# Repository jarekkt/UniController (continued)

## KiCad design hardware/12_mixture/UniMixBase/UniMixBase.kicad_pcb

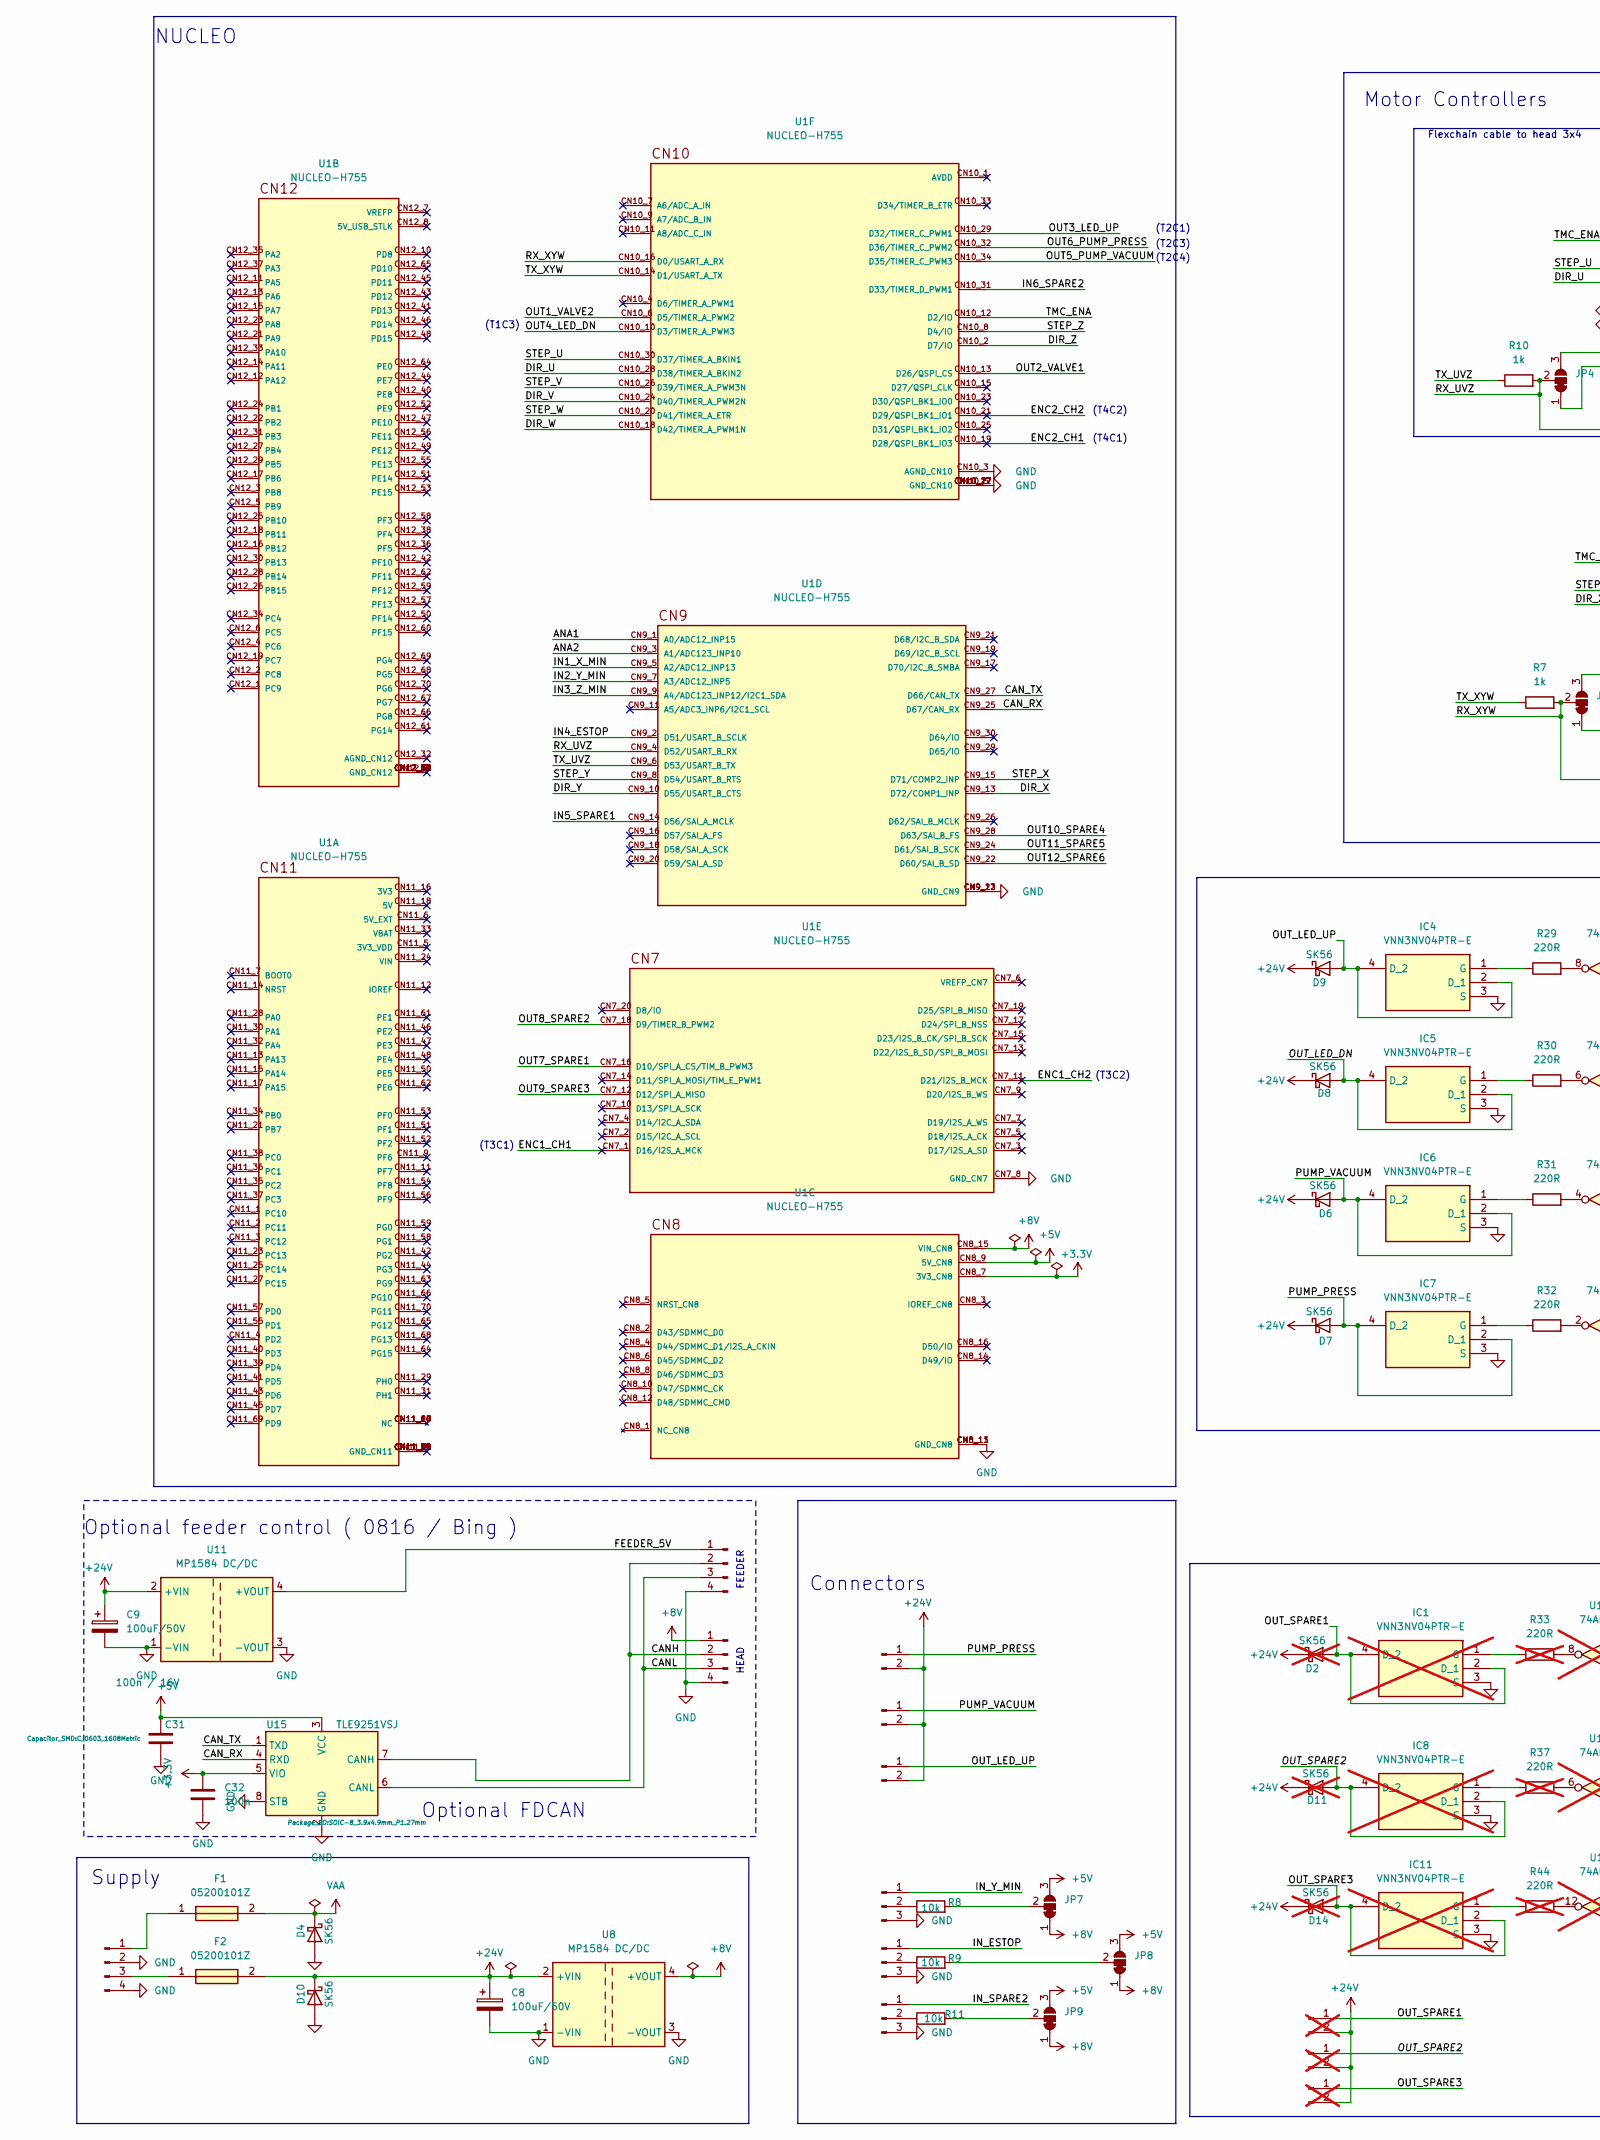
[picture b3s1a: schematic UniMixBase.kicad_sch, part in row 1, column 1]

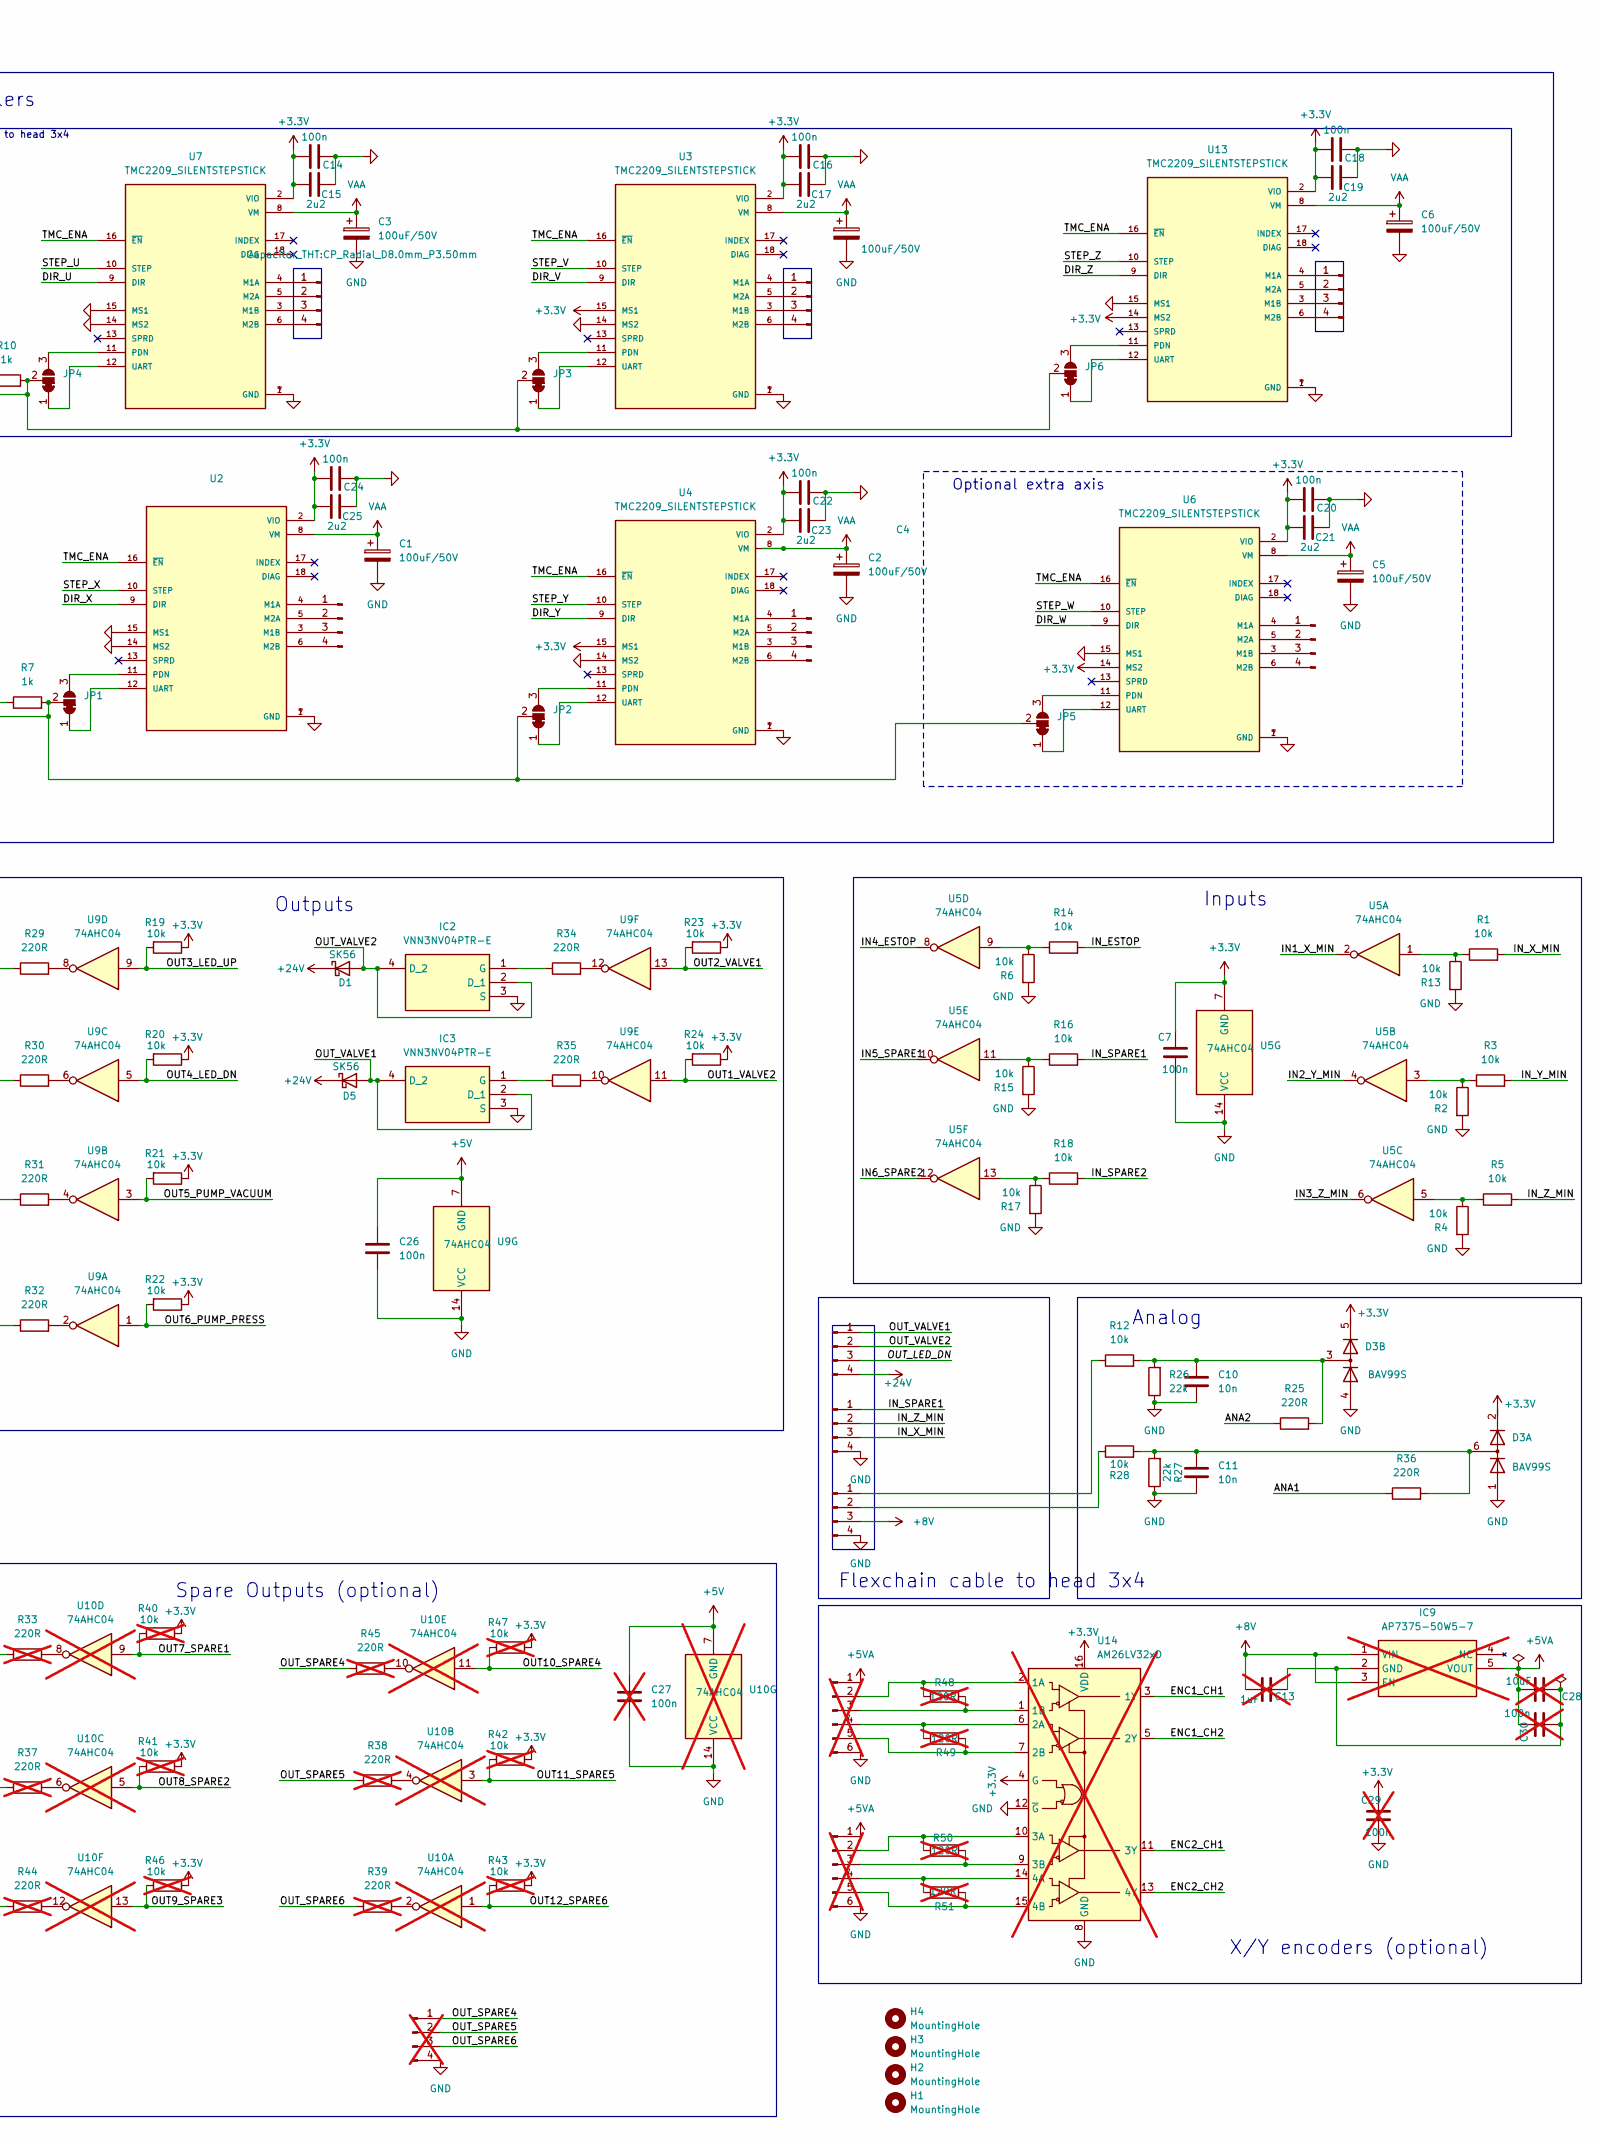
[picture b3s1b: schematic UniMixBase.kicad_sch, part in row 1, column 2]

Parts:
C1, C2, C3, C4, C5, C6, C8, C9: 100uF/50V; CP_Radial_D8.0mm_P3.50mm
C7, C14, C16, C18, C20, C22, C24, C26, C32: 100n; C_0603_1608Metric
C10, C11: 10n; C_0603_1608Metric
C13: 1uF; C_0603_1608Metric; not fitted
C15, C17, C19, C21, C23, C25: 2u2; C_0603_1608Metric
C27, C29, C30: 100n; C_0603_1608Metric; not fitted
C28: 10uF; C_1206_3216Metric; not fitted
C31: 100n / 16V; C_0603_1608Metric; Digikey CC0402KRX7R7BB104
D1, D4, D5, D6, D7, D8, D9, D10: SK56; D_SMB
D2, D11, D14: SK56; D_SMB; not fitted
D3: BAV99S; SOT-363_SC-70-6
F1, F2: 05200101Z
H1, H2, H3, H4: MountingHole; MountingHole_3.2mm_M3
IC1, IC8, IC11: VNN3NV04PTR-E; SOT230P700X180-4N; Manufacturer_Part_Number VNN3NV04PTR-E; Mouser Part Number 511-VNN3NV04PTR-E; not fitted
IC2, IC3, IC4, IC5, IC6, IC7: VNN3NV04PTR-E; SOT230P700X180-4N; Manufacturer_Part_Number VNN3NV04PTR-E; Mouser Part Number 511-VNN3NV04PTR-E
IC9: AP7375-50W5-7; SOT95P285X140-5N; Manufacturer_Part_Number AP7375-50W5-7; Mouser Part Number 621-AP7375-50W5-7; not fitted
J1, J2, J3, J4, J5, J7, J8, J9, J18, J20, J21: Conn_01x04_Male; JST_XH_B4B-XH-AM_1x04_P2.50mm_Vertical
J6, J10, J22: Conn_01x03_Pin; JST_XH_B3B-XH-A_1x03_P2.50mm_Vertical
J11, J12, J13: Conn_01x02_Male; JST_XH_B2B-XH-A_1x02_P2.50mm_Vertical; not fitted
J14: Conn_01x04_Male; JST_XH_B4B-XH-AM_1x04_P2.50mm_Vertical; not fitted
J15, J16: Conn_01x06_Male; JST_XH_B6B-XH-AM_1x06_P2.50mm_Vertical; not fitted
J24: Conn_01x04_Male; TerminalBlock_Phoenix_MKDS-1,5-4-5.08_1x04_P5.08mm_Horizont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
J31, J32, J33: Conn_01x02_Male; JST_XH_B2B-XH-A_1x02_P2.50mm_Vertical
JP1, JP2, JP3, JP4, JP5, JP6, JP7, JP8, JP9: SolderJumper_3_Bridged12; SolderJumper-3_P1.3mm_Bridged12_RoundedPad1.0x1.5mm
R1, R2, R3, R4, R5, R6, R8, R9, R11, R12, R13, R14, R15, R16, R17, R18, R19, R20, R21, R22, R23, R24, R28: 10k; R_0603_1608Metric
R7, R10: 1k; R_0603_1608Metric
R25, R29, R30, R31, R32, R34, R35, R36: 220R; R_0603_1608Metric
R26, R27: 22k; R_0603_1608Metric
R33, R37, R38, R39, R44, R45: 220R; R_0603_1608Metric; not fitted
R40, R41, R42, R43, R46, R47: 10k; R_0603_1608Metric; not fitted
R48, R49, R50, R51: 120R; R_1206_3216Metric; not fitted
U1: NUCLEO-H755; MODULE_NUCLEO-H753ZI; PARTREV Rev. 2
U2, U3, U4, U6, U7, U13: TMC2209_SILENTSTEPSTICK; MODULE_TMC2209_SILENTSTEPSTICK; PARTREV 1.20
U5, U9: 74AHC04; SOIC-14_3.9x8.7mm_P1.27mm
U8, U11: MP1584 DC/DC; MP1584_mod
U10: 74AHC04; SOIC-14_3.9x8.7mm_P1.27mm; not fitted
U14: AM26LV32xD; SOIC-16_3.9x9.9mm_P1.27mm; not fitted
U15: TLE9251VSJ; SOIC-8_3.9x4.9mm_P1.27mm; Digikey TLE9251VSJXUMA1TR-ND

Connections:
+3.3V: C7.1, C14.2, C15.2, C16.2, C17.2, C18.2, C19.2, C20.2, C21.2, C22.2, C23.2, C24.2, C25.2, C29.1, C32.1, D3.2 (K2), D3.5 (K4), R19.1, R20.1, R21.1, R22.1, R23.1, R24.1, R40.1, R41.1, R42.1, R43.1, R46.1, R47.1, U1.CN8_7 (3V3_CN8), U2.2 (VIO), U3.2 (VIO), U3.15 (MS1), U4.2 (VIO), U4.15 (MS1), U5.7 (GND), U6.2 (VIO), U6.14 (MS2), U7.2 (VIO), U13.2 (VIO), U13.14 (MS2), U14.4 (G), U14.16 (VDD), U15.5 (VIO)
+5V: C26.1, C27.1, C31.1, JP7.3 (B), JP8.3 (B), JP9.3 (B), U1.CN8_9 (5V_CN8), U9.7 (GND), U10.7 (GND), U15.3 (VCC)
+5VA: C28.1, C30.1, IC9.5 (VOUT), J15.1, J16.1
+8V: C13.1, IC9.1 (VIN), IC9.3 (EN), J8.1, J20.3, JP7.1 (A), JP8.1 (A), JP9.1 (A), U1.CN8_15 (VIN_CN8), U8.4 (+VOUT)
+24V: C8.1, C9.1, D1.1 (K), D2.1 (K), D5.1 (K), D6.1 (K), D7.1 (K), D8.1 (K), D9.1 (K), D10.1 (K), D11.1 (K), D14.1 (K), F2.2, J11.2, J12.2, J13.2, J18.4, J31.2, J32.2, J33.2, U8.2 (+VIN), U11.2 (+VIN)
/ANA1: R36.1, U1.CN9_1 (A0/ADC12_INP15)
/ANA2: R25.1, U1.CN9_3 (A1/ADC123_INP10)
/CANH: J5.2, J8.2, U15.7 (CANH)
/CANL: J5.3, J8.3, U15.6 (CANL)
/CAN_RX: U1.CN9_25 (D67/CAN_RX), U15.4 (RXD)
/CAN_TX: U1.CN9_27 (D66/CAN_TX), U15.1 (TXD)
/DIR_U: U1.CN10_28 (D38/TIMER_A_BKIN2), U7.9 (DIR)
/DIR_V: U1.CN10_24 (D40/TIMER_A_PWM2N), U3.9 (DIR)
/DIR_W: U1.CN10_18 (D42/TIMER_A_PWM1N), U6.9 (DIR)
/DIR_X: U1.CN9_13 (D72/COMP1_INP), U2.9 (DIR)
/DIR_Y: U1.CN9_10 (D55/USART_B_CTS), U4.9 (DIR)
/DIR_Z: U1.CN10_2 (D7/IO), U13.9 (DIR)
/ENC1_CH1: U1.CN7_1 (D16/I2S_A_MCK), U14.3 (1Y)
/ENC1_CH2: U1.CN7_11 (D21/I2S_B_MCK), U14.5 (2Y)
/ENC2_CH1: U1.CN10_19 (D28/QSPI_BK1_IO3), U14.11 (3Y)
/ENC2_CH2: U1.CN10_21 (D29/QSPI_BK1_IO1), U14.13 (4Y)
/FEEDER_5V: J5.1, U11.4 (+VOUT)
/IN1_X_MIN: U1.CN9_5 (A2/ADC12_INP13), U5.2
/IN2_Y_MIN: U1.CN9_7 (A3/ADC12_INP5), U5.4
/IN3_Z_MIN: U1.CN9_9 (A4/ADC123_INP12/I2C1_SDA), U5.6
/IN4_ESTOP: U1.CN9_2 (D51/USART_B_SCLK), U5.8
/IN5_SPARE1: U1.CN9_14 (D56/SAI_A_MCLK), U5.10
/IN6_SPARE2: U1.CN10_31 (D33/TIMER_D_PWM1), U5.12
/IN_ESTOP: J22.1, R14.2
/IN_SPARE1: J21.1, R16.2
/IN_SPARE2: J10.1, R18.2
/IN_X_MIN: J21.3, R1.2
/IN_Y_MIN: J6.1, R3.2
/IN_Z_MIN: J21.2, R5.2
/OUT1_VALVE2: R24.2, U1.CN10_6 (D5/TIMER_A_PWM2), U9.11
/OUT2_VALVE1: R23.2, U1.CN10_13 (D26/QSPI_CS), U9.13
/OUT3_LED_UP: R19.2, U1.CN10_29 (D32/TIMER_C_PWM1), U9.9
/OUT4_LED_DN: R20.2, U1.CN10_10 (D3/TIMER_A_PWM3), U9.5
/OUT5_PUMP_VACUUM: R21.2, U1.CN10_34 (D35/TIMER_C_PWM3), U9.3
/OUT6_PUMP_PRESS: R22.2, U1.CN10_32 (D36/TIMER_C_PWM2), U9.1
/OUT7_SPARE1: R40.2, U1.CN7_16 (D10/SPI_A_CS/TIM_B_PWM3), U10.9
/OUT8_SPARE2: R41.2, U1.CN7_18 (D9/TIMER_B_PWM2), U10.5
/OUT9_SPARE3: R46.2, U1.CN7_12 (D12/SPI_A_MISO), U10.13
/OUT10_SPARE4: R47.2, U1.CN9_28 (D63/SAI_B_FS), U10.11
/OUT11_SPARE5: R42.2, U1.CN9_24 (D61/SAI_B_SCK), U10.3
/OUT12_SPARE6: R43.2, U1.CN9_22 (D60/SAI_B_SD), U10.1
/OUT_LED_DN: D8.2 (A), IC5.2 (D_1), IC5.4 (D_2), J18.3
/OUT_LED_UP: D9.2 (A), IC4.2 (D_1), IC4.4 (D_2), J33.1
/OUT_SPARE1: D2.2 (A), IC1.2 (D_1), IC1.4 (D_2), J11.1
/OUT_SPARE2: D11.2 (A), IC8.2 (D_1), IC8.4 (D_2), J12.1
/OUT_SPARE3: D14.2 (A), IC11.2 (D_1), IC11.4 (D_2), J13.1
/OUT_SPARE4: J14.1, R45.1
/OUT_SPARE5: J14.2, R38.1
/OUT_SPARE6: J14.3, R39.1
/OUT_VALVE1: D5.2 (A), IC3.2 (D_1), IC3.4 (D_2), J18.1
/OUT_VALVE2: D1.2 (A), IC2.2 (D_1), IC2.4 (D_2), J18.2
/PUMP_PRESS: D7.2 (A), IC7.2 (D_1), IC7.4 (D_2), J32.1
/PUMP_VACUUM: D6.2 (A), IC6.2 (D_1), IC6.4 (D_2), J31.1
/RX_UVZ: JP3.2 (C), JP4.2 (C), JP6.2 (C), R10.2, U1.CN9_4 (D52/USART_B_RX)
/RX_XYW: JP1.2 (C), JP2.2 (C), JP5.2 (C), R7.2, U1.CN10_16 (D0/USART_A_RX)
/STEP_U: U1.CN10_30 (D37/TIMER_A_BKIN1), U7.10 (STEP)
/STEP_V: U1.CN10_26 (D39/TIMER_A_PWM3N), U3.10 (STEP)
/STEP_W: U1.CN10_20 (D41/TIMER_A_ETR), U6.10 (STEP)
/STEP_X: U1.CN9_15 (D71/COMP2_INP), U2.10 (STEP)
/STEP_Y: U1.CN9_8 (D54/USART_B_RTS), U4.10 (STEP)
/STEP_Z: U1.CN10_8 (D4/IO), U13.10 (STEP)
/TMC_ENA: U1.CN10_12 (D2/IO), U2.16 (~EN), U3.16 (~EN), U4.16 (~EN), U6.16 (~EN), U7.16 (~EN), U13.16 (~EN)
/TX_UVZ: R10.1, U1.CN9_6 (D53/USART_B_TX)
/TX_XYW: R7.1, U1.CN10_14 (D1/USART_A_TX)
GND: C1.2, C2.2, C3.2, C4.2, C5.2, C6.2, C7.2, C8.2, C9.2, C10.2, C11.2, C14.1, C15.1, C16.1, C17.1, C18.1, C19.1, C20.1, C21.1, C22.1, C23.1, C24.1, C25.1, C26.2, C27.2, C29.2, C31.2, C32.2, D3.1 (A1), D3.4 (A3), D4.2 (A), D10.2 (A), IC1.3 (S), IC2.3 (S), IC3.3 (S), IC4.3 (S), IC5.3 (S), IC6.3 (S), IC7.3 (S), IC8.3 (S), IC11.3 (S), J5.4, J6.3, J8.4, J10.3, J14.4, J15.6, J16.6, J20.4, J21.4, J22.3, J24.2, J24.4, R2.2, R4.2, R6.2, R13.2, R15.2, R17.2, R26.1, R27.1, U1.CN7_8 (GND_CN7), U1.CN8_11 (GND_CN8), U1.CN8_13 (GND_CN8), U1.CN9_12 (GND_CN9), U1.CN9_23 (GND_CN9), U1.CN10_3 (AGND_CN10), U1.CN10_5 (GND_CN10), U1.CN10_17 (GND_CN10), U1.CN10_22 (GND_CN10), U1.CN10_27 (GND_CN10), U2.1 (GND), U2.7 (GND), U2.14 (MS2), U2.15 (MS1), U3.1 (GND), U3.7 (GND), U3.14 (MS2), U4.1 (GND), U4.7 (GND), U4.14 (MS2), U5.14 (VCC), U6.1 (GND), U6.7 (GND), U6.15 (MS1), U7.1 (GND), U7.7 (GND), U7.14 (MS2), U7.15 (MS1), U8.1 (-VIN), U8.3 (-VOUT), U9.14 (VCC), U10.14 (VCC), U11.1 (-VIN), U11.3 (-VOUT), U13.1 (GND), U13.7 (GND), U13.15 (MS1), U14.8 (GND), U14.12 (~G), U15.2 (GND), U15.8 (STB)
unnamed: C11.1, D3.6 (K3A4), R27.2, R28.2, R36.2
unnamed: C10.1, D3.3 (K1A2), R12.2, R25.2, R26.2
unnamed: IC1.1 (G), R33.1
unnamed: IC2.1 (G), R34.1
unnamed: IC3.1 (G), R35.1
unnamed: IC4.1 (G), R29.1
unnamed: IC5.1 (G), R30.1
unnamed: IC6.1 (G), R31.1
unnamed: IC7.1 (G), R32.1
unnamed: IC8.1 (G), R37.1
unnamed: C13.2, C28.2, C30.2, IC9.2 (GND)
unnamed: IC11.1 (G), R44.1
unnamed: J1.1, U3.4 (M1A)
unnamed: J1.2, U3.5 (M2A)
unnamed: J1.3, U3.3 (M1B)
unnamed: J1.4, U3.6 (M2B)
unnamed: J2.1, U4.4 (M1A)
unnamed: J2.2, U4.5 (M2A)
unnamed: J2.3, U4.3 (M1B)
unnamed: J2.4, U4.6 (M2B)
unnamed: J3.1, U13.4 (M1A)
unnamed: J3.2, U13.5 (M2A)
unnamed: J3.3, U13.3 (M1B)
unnamed: J3.4, U13.6 (M2B)
unnamed: J4.1, U7.4 (M1A)
unnamed: J4.2, U7.5 (M2A)
unnamed: J4.3, U7.3 (M1B)
unnamed: J4.4, U7.6 (M2B)
unnamed: J6.2, R8.1
unnamed: J7.1, U2.4 (M1A)
unnamed: J7.2, U2.5 (M2A)
unnamed: J7.3, U2.3 (M1B)
unnamed: J7.4, U2.6 (M2B)
unnamed: J9.1, U6.4 (M1A)
unnamed: J9.2, U6.5 (M2A)
unnamed: J9.3, U6.3 (M1B)
unnamed: J9.4, U6.6 (M2B)
unnamed: J10.2, R11.1
unnamed: J15.2, R48.1, U14.2 (1A)
unnamed: J15.3, R48.2, U14.1 (1B)
unnamed: J15.4, R49.1, U14.6 (2A)
unnamed: J15.5, R49.2, U14.7 (2B)
unnamed: J16.2, R50.1, U14.10 (3A)
unnamed: J16.3, R50.2, U14.9 (3B)
unnamed: J16.4, R51.1, U14.14 (4A)
unnamed: J16.5, R51.2, U14.15 (4B)
unnamed: J20.1, R12.1
unnamed: J20.2, R28.1
unnamed: J22.2, R9.1
unnamed: F1.1, J24.1
unnamed: F2.1, J24.3
unnamed: JP1.1 (A), U2.12 (UART)
unnamed: JP1.3 (B), U2.11 (PDN)
unnamed: JP2.1 (A), U4.12 (UART)
unnamed: JP2.3 (B), U4.11 (PDN)
unnamed: JP3.1 (A), U3.12 (UART)
unnamed: JP3.3 (B), U3.11 (PDN)
unnamed: JP4.1 (A), U7.12 (UART)
unnamed: JP4.3 (B), U7.11 (PDN)
unnamed: JP5.1 (A), U6.12 (UART)
unnamed: JP5.3 (B), U6.11 (PDN)
unnamed: JP6.1 (A), U13.12 (UART)
unnamed: JP6.3 (B), U13.11 (PDN)
unnamed: JP7.2 (C), R8.2
unnamed: JP8.2 (C), R9.2
unnamed: JP9.2 (C), R11.2
unnamed: R1.1, R13.1, U5.1
unnamed: R2.1, R3.1, U5.3
unnamed: R4.1, R5.1, U5.5
unnamed: R6.1, R14.1, U5.9
unnamed: R15.1, R16.1, U5.11
unnamed: R17.1, R18.1, U5.13
unnamed: R29.2, U9.8
unnamed: R30.2, U9.6
unnamed: R31.2, U9.4
unnamed: R32.2, U9.2
unnamed: R33.2, U10.8
unnamed: R34.2, U9.12
unnamed: R35.2, U9.10
unnamed: R37.2, U10.6
unnamed: R38.2, U10.4
unnamed: R39.2, U10.2
unnamed: R44.2, U10.12
unnamed: R45.2, U10.10
VAA: C1.1, C2.1, C3.1, C4.1, C5.1, C6.1, D4.1 (K), F1.2, U2.8 (VM), U3.8 (VM), U4.8 (VM), U6.8 (VM), U7.8 (VM), U13.8 (VM)

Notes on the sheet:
Optional extra axis
(T1C3)
FEEDER
Motor Controllers
(T4C2)
(T3C2)
Optional FDCAN
(T2C4)
Analog
Optional feeder control ( 0816 / Bing )
Inputs
HEAD
NUCLEO
(T2C3)
Outputs
Flexchain cable to head 3x4
Supply
Connectors
X/Y encoders (optional)
(T3C1)
(T4C1)
(T2C1)
Spare Outputs (optional)

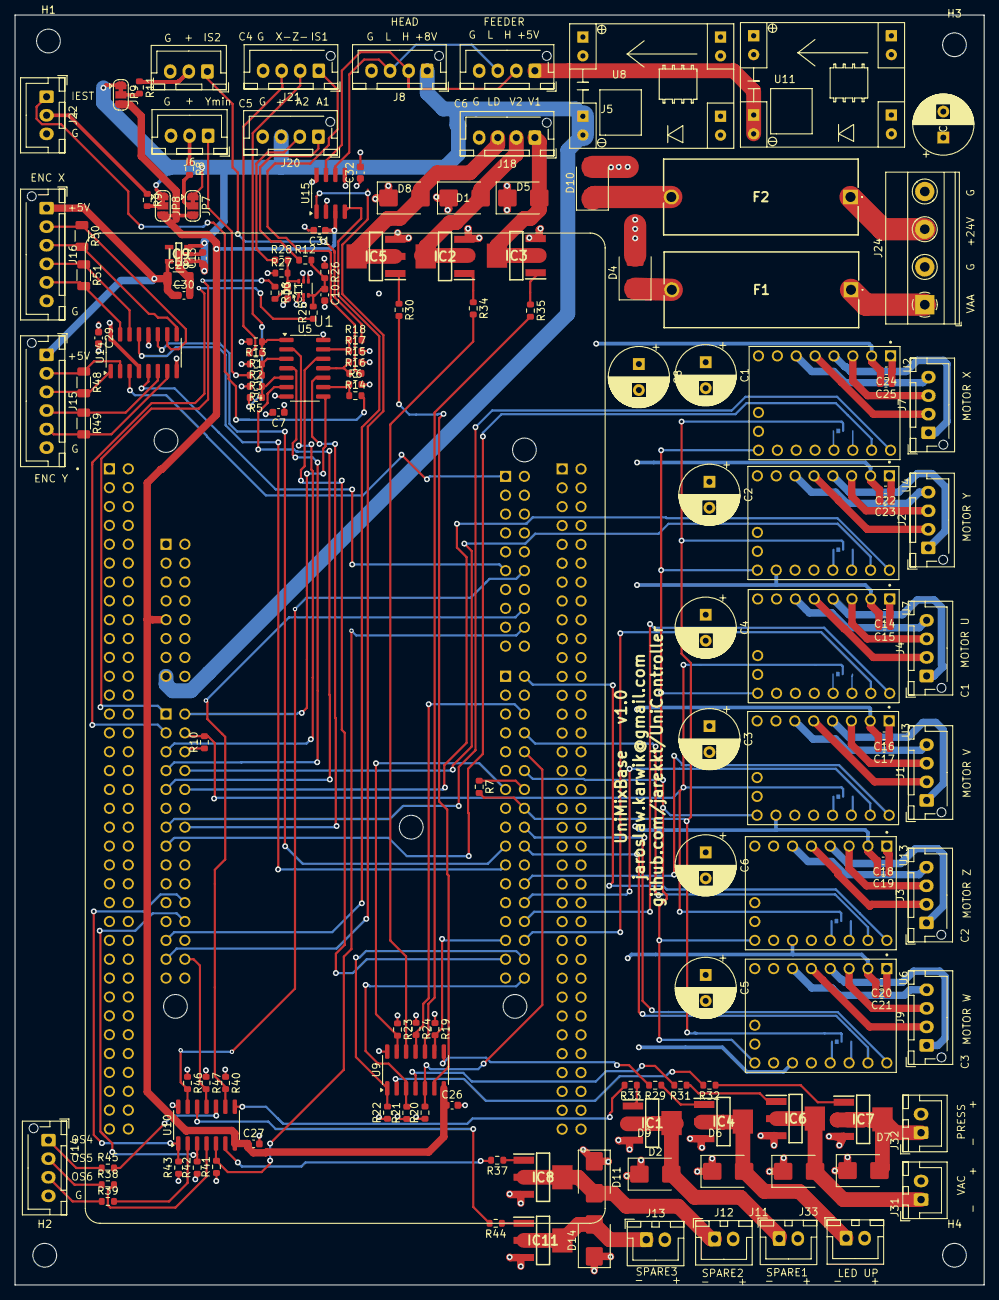
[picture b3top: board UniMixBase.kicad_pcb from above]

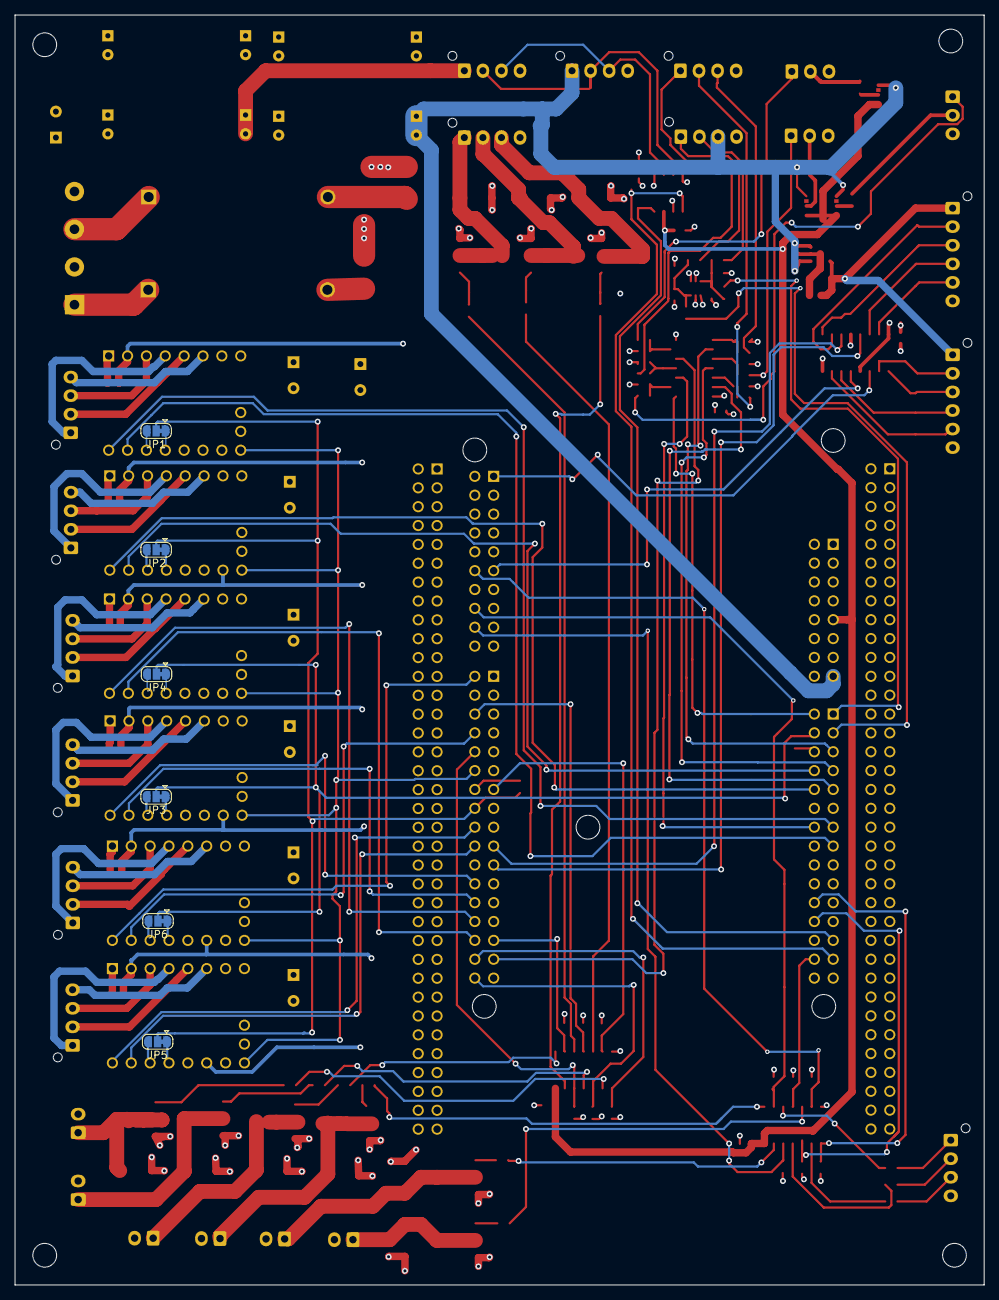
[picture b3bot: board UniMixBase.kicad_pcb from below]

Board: 4 copper layers, 130.5 x 171.0 mm, 157 parts (6 on the bottom side), 155 nets.

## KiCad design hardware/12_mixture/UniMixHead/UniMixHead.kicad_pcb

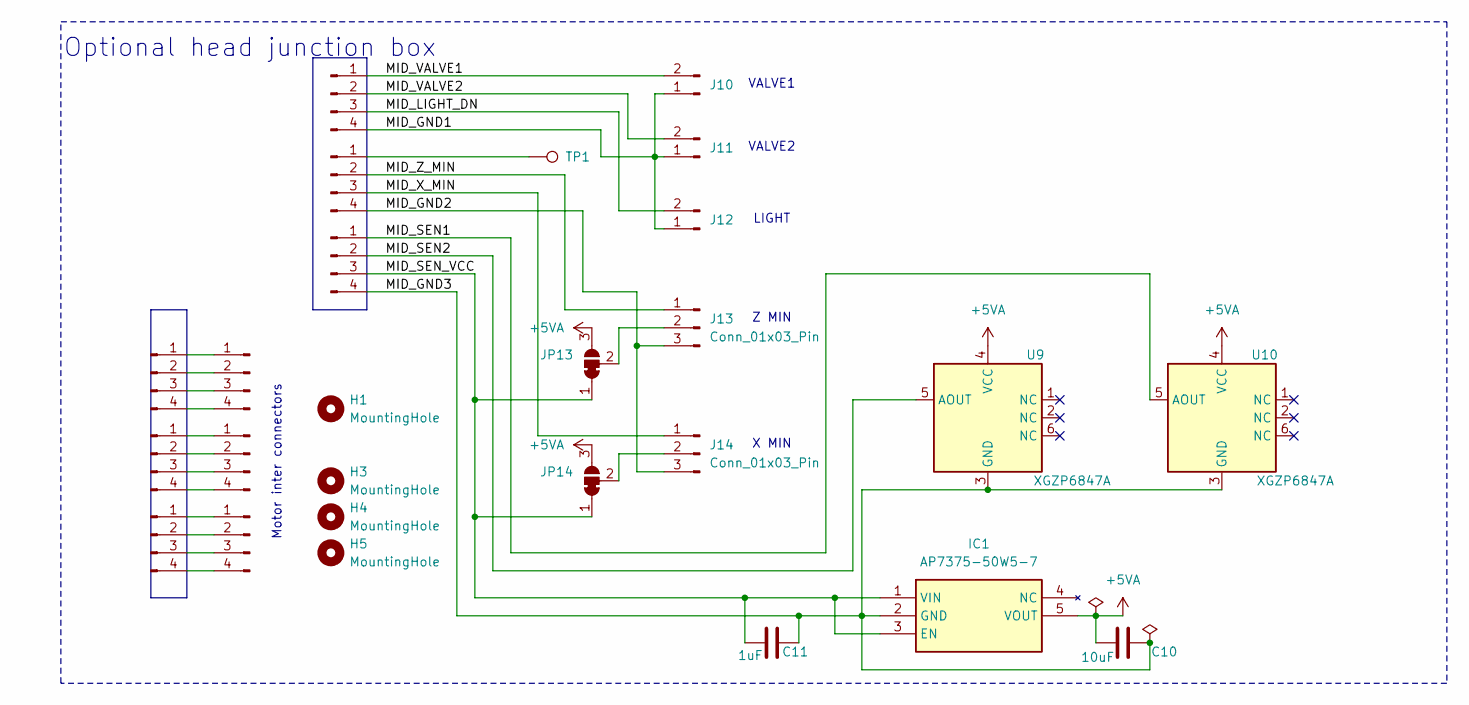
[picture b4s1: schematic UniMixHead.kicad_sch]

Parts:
C10: 10uF; C_1206_3216Metric
C11: 1uF; C_0603_1608Metric
H1, H3, H4, H5: MountingHole; MountingHole_3.2mm_M3
IC1: AP7375-50W5-7; SOT95P285X140-5N; Manufacturer_Part_Number AP7375-50W5-7; Mouser Part Number 621-AP7375-50W5-7
J10, J11, J12: Conn_01x02_Male; JST_XH_B2B-XH-A_1x02_P2.50mm_Vertical
J13, J14: Conn_01x03_Pin; JST_XH_B3B-XH-A_1x03_P2.50mm_Vertical
J16, J17, J19, J25, J26, J27, J28, J29, J30: Conn_01x04_Male; JST_XH_B4B-XH-AM_1x04_P2.50mm_Vertical
JP13, JP14: SolderJumper_3_Bridged12; SolderJumper-3_P1.3mm_Bridged12_RoundedPad1.0x1.5mm
TP1: TestPoint; PinHeader_1x01_P1.00mm_Vertical
U9, U10: XGZP6847A; DIP-6_W10.16mm

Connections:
+5VA: C10.1, IC1.5 (VOUT), JP13.3 (B), JP14.3 (B), U9.4 (VCC), U10.4 (VCC)
/MID_GND1: J10.1, J11.1, J12.1, J16.4
/MID_GND2: J13.3, J14.3, J19.4
/MID_GND3: C10.2, C11.2, IC1.2 (GND), J17.4, U9.3 (GND), U10.3 (GND)
/MID_LIGHT_DN: J12.2, J16.3
/MID_SEN1: J17.1, U10.5 (AOUT)
/MID_SEN2: J17.2, U9.5 (AOUT)
/MID_SEN_VCC: C11.1, IC1.1 (VIN), IC1.3 (EN), J17.3, JP13.1 (A), JP14.1 (A)
/MID_VALVE1: J10.2, J16.1
/MID_VALVE2: J11.2, J16.2
/MID_X_MIN: J14.1, J19.3
/MID_Z_MIN: J13.1, J19.2
unnamed: J13.2, JP13.2 (C)
unnamed: J14.2, JP14.2 (C)
unnamed: J19.1, TP1.1
unnamed: J25.1, J28.1
unnamed: J25.2, J28.2
unnamed: J25.3, J28.3
unnamed: J25.4, J28.4
unnamed: J26.1, J29.1
unnamed: J26.2, J29.2
unnamed: J26.3, J29.3
unnamed: J26.4, J29.4
unnamed: J27.1, J30.1
unnamed: J27.2, J30.2
unnamed: J27.3, J30.3
unnamed: J27.4, J30.4

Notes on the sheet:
Z MIN
LIGHT
VALVE1
X MIN
VALVE2
Motor inter connectors
Optional head junction box

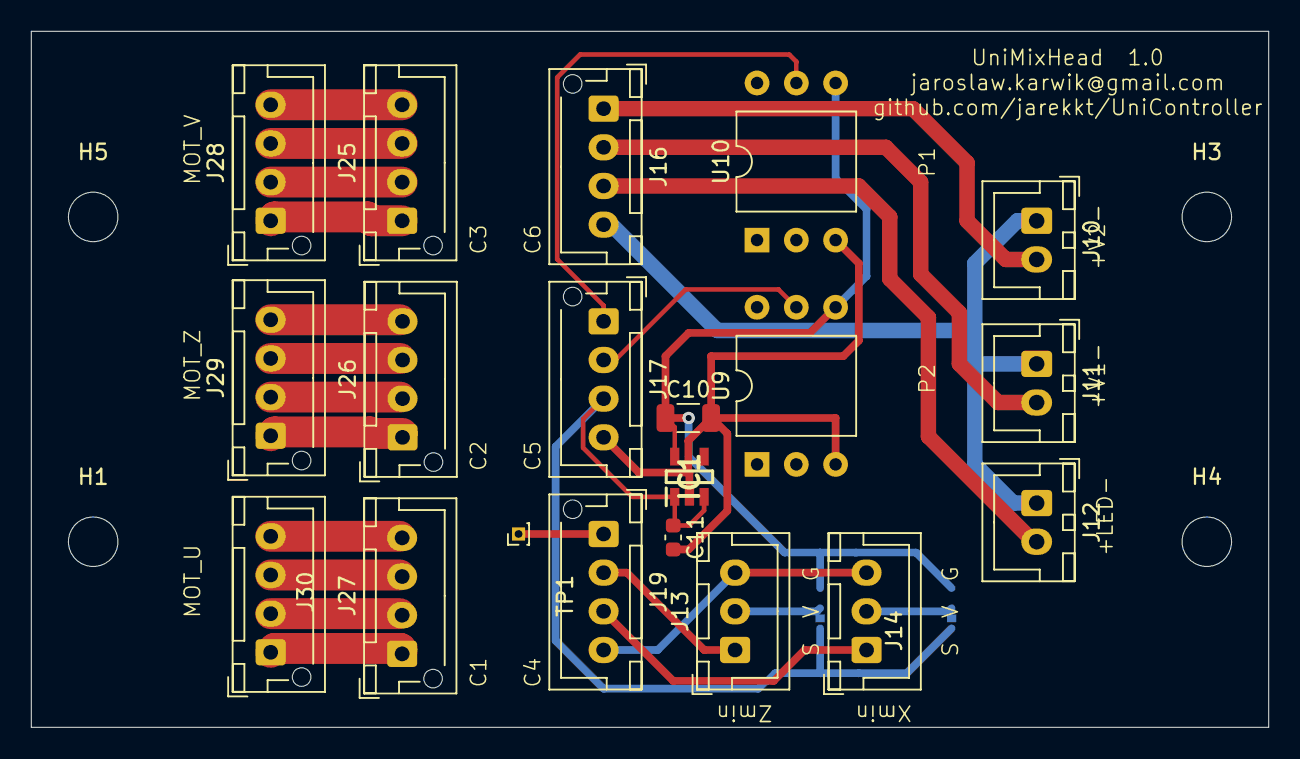
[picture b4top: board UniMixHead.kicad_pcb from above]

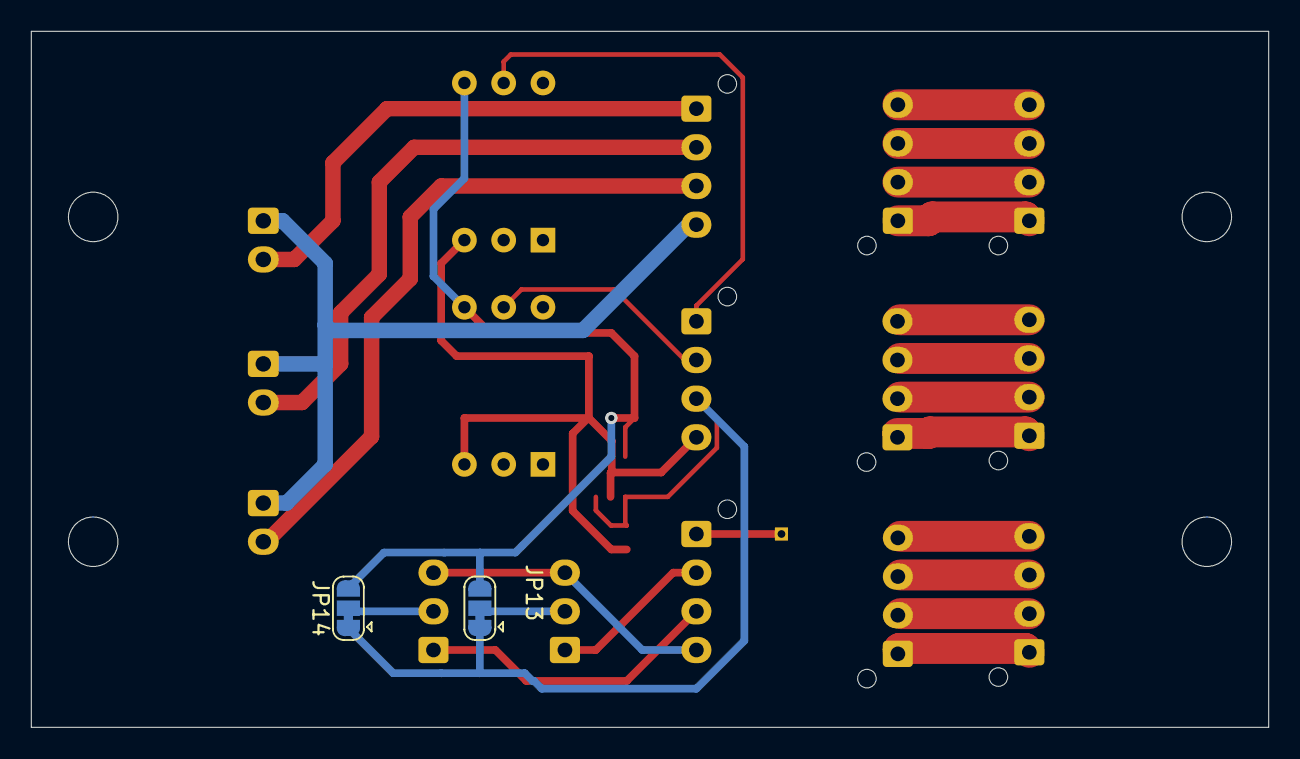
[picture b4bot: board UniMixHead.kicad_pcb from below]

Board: 2 copper layers, 80.0 x 45.0 mm, 26 parts (2 on the bottom side), 27 nets.
